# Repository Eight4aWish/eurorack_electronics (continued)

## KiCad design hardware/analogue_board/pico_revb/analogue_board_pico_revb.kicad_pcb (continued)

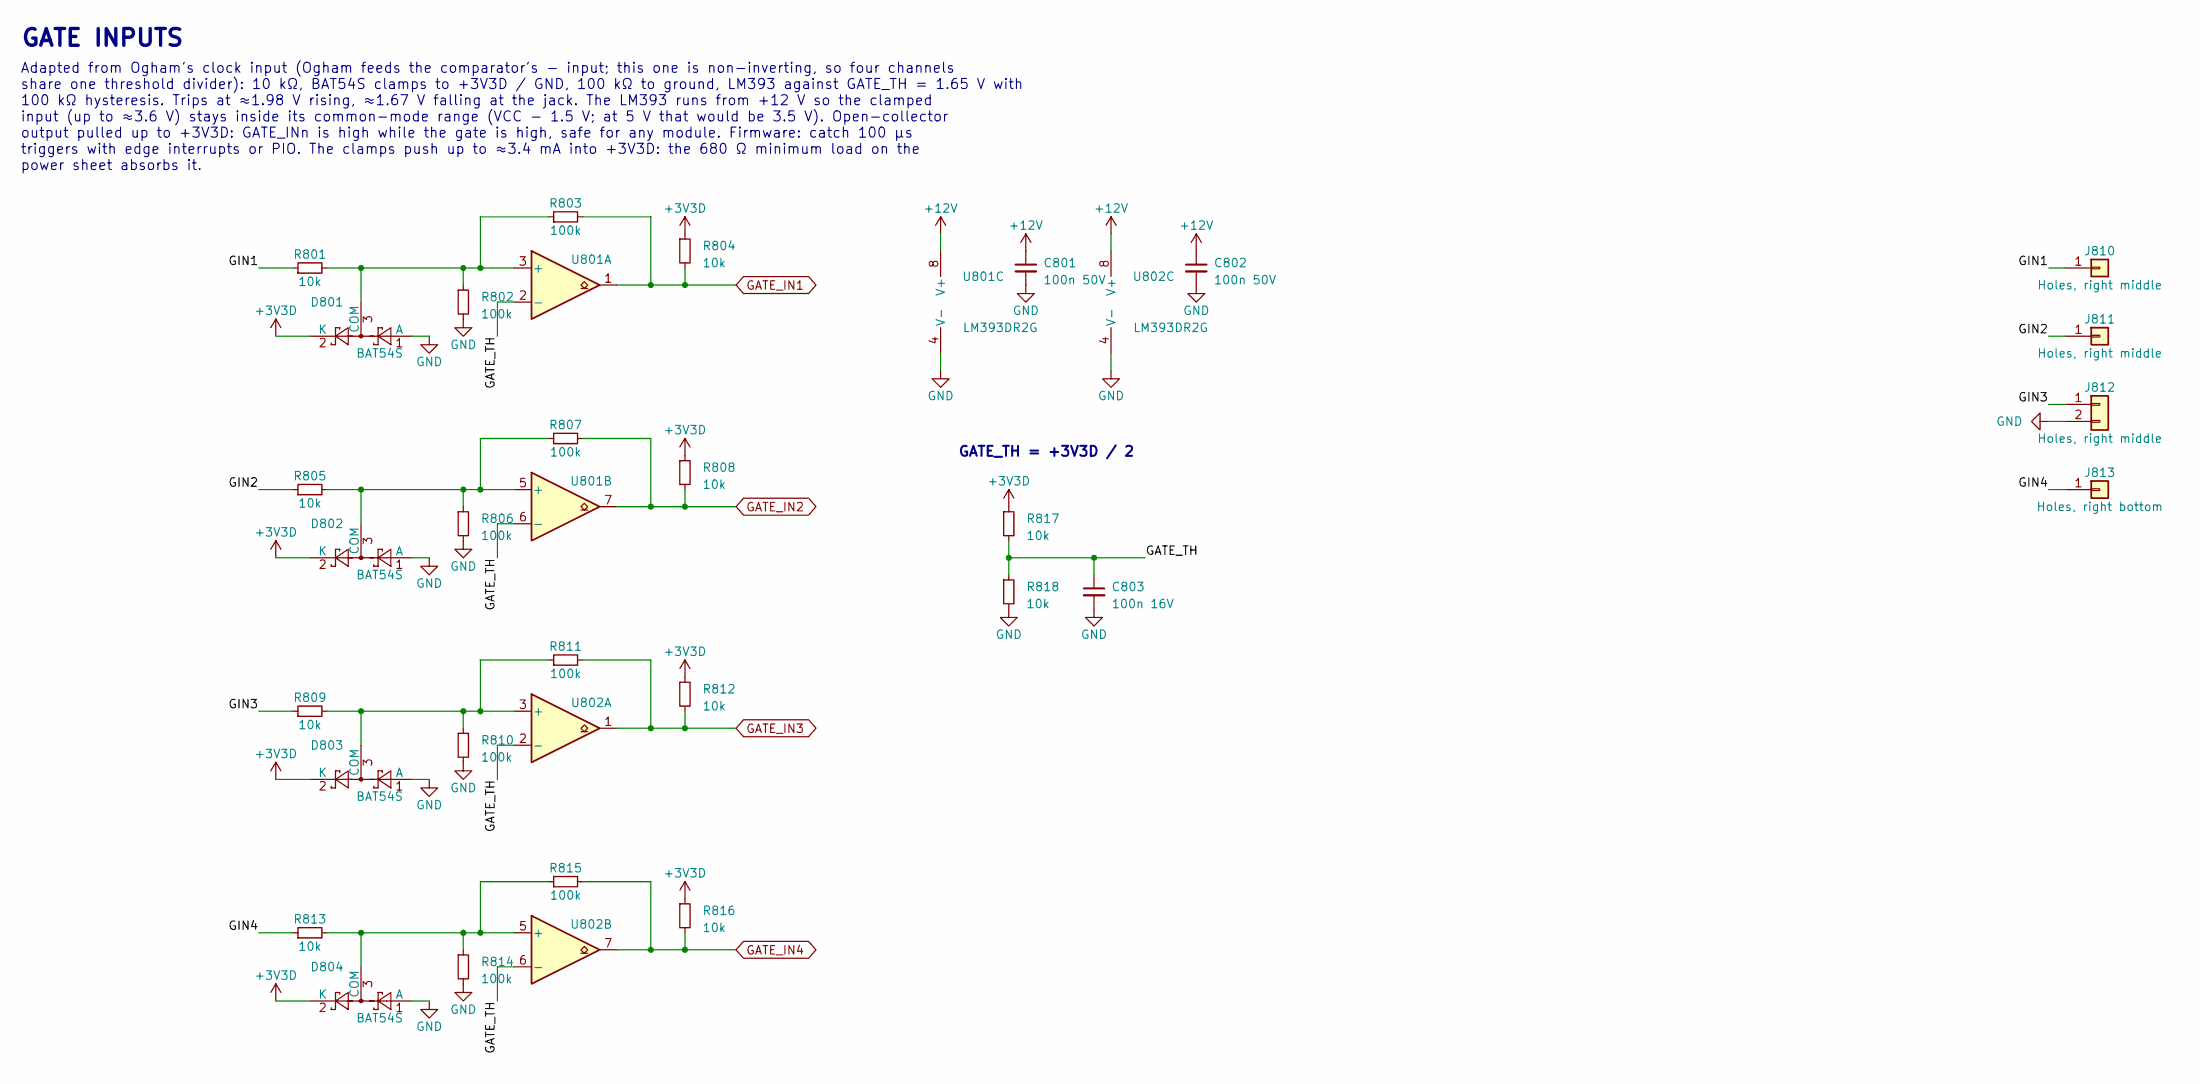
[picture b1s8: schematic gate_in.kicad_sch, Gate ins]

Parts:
C801, C802: 100n 50V; C_0603_1608Metric; Voltage 50V; LCSC C14663
C803: 100n 16V; C_0402_1005Metric; Voltage 16V; LCSC C1525
D801, D802, D803, D804: BAT54S; SOT-23; MPN BAT54S; LCSC C408389
J810, J811: Holes, right middle; WiringHoles_1x01; JLC bare holes
J812: Holes, right middle; WiringHoles_1x02_G2; JLC bare holes
J813: Holes, right bottom; WiringHoles_1x01; JLC bare holes
R801, R804, R805, R808, R809, R812, R813, R816, R817, R818: 10k; R_0402_1005Metric; Tolerance 1%; LCSC C25744
R802, R803, R806, R807, R810, R811, R814, R815: 100k; R_0402_1005Metric; Tolerance 1%; LCSC C25741
U801, U802: LM393DR2G; SOIC-8_3.9x4.9mm_P1.27mm; MPN LM393DR2G; LCSC C7955

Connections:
+3V3D: D801.2 (K), D802.2 (K), D803.2 (K), D804.2 (K), R804.1, R808.1, R812.1, R816.1, R817.1; also elsewhere on the board
+12V: C801.1, C802.1, U801.8 (V+), U802.8 (V+); also elsewhere on the board
/Gate ins/GATE_TH: C803.1, R817.2, R818.1, U801.2 (-), U801.6 (-), U802.2 (-), U802.6 (-)
/Gate ins/GIN1: J810.1, R801.1
/Gate ins/GIN2: J811.1, R805.1
/Gate ins/GIN3: J812.1, R809.1
/Gate ins/GIN4: J813.1, R813.1
GATE_IN1: R803.2, R804.2, U801.1; also elsewhere on the board
GATE_IN2: R807.2, R808.2, U801.7; also elsewhere on the board
GATE_IN3: R811.2, R812.2, U802.1; also elsewhere on the board
GATE_IN4: R815.2, R816.2, U802.7; also elsewhere on the board
GND: C801.2, C802.2, C803.2, D801.1 (A), D802.1 (A), D803.1 (A), D804.1 (A), J812.2, R802.2, R806.2, R810.2, R814.2, R818.2, U801.4 (V-), U802.4 (V-); also elsewhere on the board
unnamed: D801.3 (COM), R801.2, R802.1, R803.1, U801.3 (+)
unnamed: D802.3 (COM), R805.2, R806.1, R807.1, U801.5 (+)
unnamed: D803.3 (COM), R809.2, R810.1, R811.1, U802.3 (+)
unnamed: D804.3 (COM), R813.2, R814.1, R815.1, U802.5 (+)

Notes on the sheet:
GATE INPUTS
Adapted from Ogham's clock input (Ogham feeds the comparator's − input; this one is non-inverting, so four channels share one threshold divider): 10 kΩ, BAT54S clamps to +3V3D / GND, 100 kΩ to ground, LM393 against GATE_TH = 1.65 V with 100 kΩ hysteresis. Trips at ≈1.98 V rising, ≈1.67 V falling at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
GATE_TH = +3V3D / 2

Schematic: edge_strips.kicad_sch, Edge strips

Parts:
FID901, FID902, FID903: Fiducial; Fiducial_1mm_Mask2mm; JLC bare pad
J901: Edge strip, left (10HP); EdgeStrip_40_Left_10HP; JLC bare holes
J902: Edge strip, right; EdgeStrip_40_Right; JLC bare holes

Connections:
/Edge strips/DECK_L1: J901.1 (D1), J901.41 (W1)
/Edge strips/DECK_L2: J901.2 (D2), J901.42 (W2)
/Edge strips/DECK_L3: J901.3 (D3), J901.43 (W3)
/Edge strips/DECK_L4: J901.4 (D4), J901.44 (W4)
/Edge strips/DECK_L5: J901.5 (D5), J901.45 (W5)
/Edge strips/DECK_L6: J901.6 (D6), J901.46 (W6)
/Edge strips/DECK_L7: J901.7 (D7), J901.47 (W7)
/Edge strips/DECK_L8: J901.8 (D8), J901.48 (W8)
/Edge strips/DECK_L9: J901.9 (D9), J901.49 (W9)
/Edge strips/DECK_L17: J901.17 (D17), J901.57 (W17)
/Edge strips/DECK_L18: J901.18 (D18), J901.58 (W18)
/Edge strips/DECK_L19: J901.19 (D19), J901.59 (W19)
/Edge strips/DECK_L20: J901.20 (D20), J901.60 (W20)
/Edge strips/DECK_L21: J901.21 (D21), J901.61 (W21)
/Edge strips/DECK_L22: J901.22 (D22), J901.62 (W22)
/Edge strips/DECK_L23: J901.23 (D23), J901.63 (W23)
/Edge strips/DECK_L24: J901.24 (D24), J901.64 (W24)
/Edge strips/DECK_L25: J901.25 (D25), J901.65 (W25)
/Edge strips/DECK_L32: J901.32 (D32), J901.72 (W32)
/Edge strips/DECK_L33: J901.33 (D33), J901.73 (W33)
/Edge strips/DECK_L34: J901.34 (D34), J901.74 (W34)
/Edge strips/DECK_L35: J901.35 (D35), J901.75 (W35)
/Edge strips/DECK_L36: J901.36 (D36), J901.76 (W36)
/Edge strips/DECK_L37: J901.37 (D37), J901.77 (W37)
/Edge strips/DECK_L38: J901.38 (D38), J901.78 (W38)
/Edge strips/DECK_L39: J901.39 (D39), J901.79 (W39)
/Edge strips/DECK_L40: J901.40 (D40), J901.80 (W40)
/Edge strips/DECK_R1: J902.1 (D1), J902.41 (W1)
/Edge strips/DECK_R2: J902.2 (D2), J902.42 (W2)
/Edge strips/DECK_R3: J902.3 (D3), J902.43 (W3)
/Edge strips/DECK_R4: J902.4 (D4), J902.44 (W4)
/Edge strips/DECK_R5: J902.5 (D5), J902.45 (W5)
/Edge strips/DECK_R6: J902.6 (D6), J902.46 (W6)
/Edge strips/DECK_R7: J902.7 (D7), J902.47 (W7)
/Edge strips/DECK_R8: J902.8 (D8), J902.48 (W8)
/Edge strips/DECK_R9: J902.9 (D9), J902.49 (W9)
/Edge strips/DECK_R17: J902.17 (D17), J902.57 (W17)
/Edge strips/DECK_R18: J902.18 (D18), J902.58 (W18)
/Edge strips/DECK_R19: J902.19 (D19), J902.59 (W19)
/Edge strips/DECK_R20: J902.20 (D20), J902.60 (W20)
/Edge strips/DECK_R21: J902.21 (D21), J902.61 (W21)
/Edge strips/DECK_R22: J902.22 (D22), J902.62 (W22)
/Edge strips/DECK_R23: J902.23 (D23), J902.63 (W23)
/Edge strips/DECK_R24: J902.24 (D24), J902.64 (W24)
/Edge strips/DECK_R25: J902.25 (D25), J902.65 (W25)
/Edge strips/DECK_R32: J902.32 (D32), J902.72 (W32)
/Edge strips/DECK_R33: J902.33 (D33), J902.73 (W33)
/Edge strips/DECK_R34: J902.34 (D34), J902.74 (W34)
/Edge strips/DECK_R35: J902.35 (D35), J902.75 (W35)
/Edge strips/DECK_R36: J902.36 (D36), J902.76 (W36)
/Edge strips/DECK_R37: J902.37 (D37), J902.77 (W37)
/Edge strips/DECK_R38: J902.38 (D38), J902.78 (W38)
/Edge strips/DECK_R39: J902.39 (D39), J902.79 (W39)
/Edge strips/DECK_R40: J902.40 (D40), J902.80 (W40)

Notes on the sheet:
EDGE STRIPS
Two n8synth-style edge strips, 40 positions each at 2.54 mm. Each position is an outer hole (the deck's header pin, Dn) joined to an inner hole (a wiring point, Wn) by the net DECK_Ln / DECK_Rn: one pin per hole. Nothing else on the board connects to them: each module is wired by hand from the chan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
Fiducials for JLCPCB assembly
Hardware licence: CC BY-SA 4.0 (LICENSE in hardware/analogue_board).

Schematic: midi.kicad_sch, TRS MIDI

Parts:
C1001, C1002: 100n 16V; C_0402_1005Metric; Voltage 16V; LCSC C1525
C1003: 100n 50V; C_0603_1608Metric; Voltage 50V; LCSC C14663
D1001: BAT54S; SOT-23; MPN BAT54S; LCSC C408389
D1002: 1N4148WS; D_SOD-323; MPN 1N4148WS; LCSC C2128
J1001: TRS MIDI out holes; WiringHoles_1x02; JLC bare holes
J1002: TRS MIDI in holes; WiringHoles_1x03; JLC bare holes
R1001, R1008, R1009: 1k; R_0402_1005Metric; Tolerance 1%; LCSC C11702
R1002: 10k; R_0402_1005Metric; Tolerance 1%; LCSC C25744
R1003, R1004, R1005, R1006: 100R; R_1206_3216Metric; Tolerance 1%; LCSC C17901
R1007: 220R; R_0805_2012Metric; Tolerance 1%; LCSC C17557
U1001: SN74AHCT1G125DBVR; SOT-23-5; MPN SN74AHCT1G125DBVR; LCSC C7484
U1002: H11L1SR2M; SMDIP-6_W9.53mm; MPN H11L1SR2M; LCSC C20082

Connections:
+3V3D: C1002.1, R1002.1, R1008.1, U1002.6; also elsewhere on the board
+5VD: C1001.1, D1001.2 (K), R1005.1, U1001.5 (VCC); also elsewhere on the board
/TRS MIDI/MI_R: J1002.2, R1007.1
/TRS MIDI/MI_S: C1003.1, J1002.3
/TRS MIDI/MI_T: D1002.2 (A), J1002.1, U1002.2
/TRS MIDI/MO_R: J1001.2, R1006.2
/TRS MIDI/MO_T: J1001.1, R1004.2
GND: C1001.2, C1002.2, C1003.2, D1001.1 (A), U1001.1, U1001.3 (GND), U1002.5; also elsewhere on the board
MIDI_RX: R1009.2; also elsewhere on the board
MIDI_TX: R1001.1; also elsewhere on the board
unnamed: D1001.3 (COM), R1003.1, U1001.4
unnamed: D1002.1 (K), R1007.2, U1002.1
unnamed: R1001.2, R1002.2, U1001.2
unnamed: R1003.2, R1004.1
unnamed: R1005.2, R1006.1
unnamed: R1008.2, R1009.1, U1002.4

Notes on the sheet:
TRS MIDI IN AND OUT
MIDI 1.0 over 3.5 mm TRS, Type A (MIDI Association RP-054): tip = current sink (DIN pin 5), ring = current source (DIN pin 4), sleeve = shield (DIN pin 2). Electrical values per CA-033 (2014). Wired straight to the module's UART pins 1 and 2 (TX, RX), with no links. Review: docs/analogue_board_revi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
MIDI OUT: 3.3 V UART → 74AHCT1G125 at +5VD → 2 × 100 Ω per leg (1206) → TRS. Idle high = no loop current. A mono cable shorting ring to sleeve draws 25 mA from the buck; each 100 Ω sees 64 mW.
MIDI IN: ring → 220 Ω → H11L1 LED → tip; 1N4148WS across the LED for reverse polarity. H11L1 switches at 1.6 mA (a worst-case 3.3 V sender still gives ≈4.5 mA). Output pulled up by 1 kΩ to +3V3D, then 1 kΩ to the module pin. The IN jack's sleeve is NOT grounded (CA-033: no ground loop): wire it to 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
WIRING (two stereo jacks in deck cells): OUT: tip → MO_T, ring → MO_R, sleeve → the deck's D (ground) pad. IN: tip → MI_T, ring → MI_R, sleeve → MI_S or open: NOT to D. Type B gear: swap that jack's tip and ring wires. Bring-up: loop OUT to IN with a stereo cable; ≈1.2-1.3 V across the 220 Ω while 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

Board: 4 copper layers, 361 parts (177 on the bottom side), 249 nets, no tracks yet.

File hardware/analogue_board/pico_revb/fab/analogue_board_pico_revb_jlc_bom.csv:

Comment,Designator,Footprint,LCSC Part #
10u 50V,"C201,C203,C205,C206",C_1206_3216Metric,C13585
100n 50V,"C202,C204,C207,C215,C319,C320,C416,C417,C419,C420,C512,C513,C514,C515,C801,C802,C1003",C_0603_1608Metric,C14663
100n 16V,"C208,C212,C217,C302,C304,C306,C309,C312,C405,C418,C421,C502,C602,C604,C605,C606,C607,C608,C609,C610,C611,C701,C702,C703,C704,C705,C708,C709,C803,C1001,C1002",C_0402_1005Metric,C1525
22u 25V,"C210,C211,C407",C_1206_3216Metric,C12891
10u 25V,"C213,C216,C219,C221,C222,C301,C303,C305,C403,C404,C408,C501,C603",C_0805_2012Metric,C15850
1u 50V,"C214,C401,C402,C406",C_0603_1608Metric,C15849
1u 25V,"C218,C220,C503,C601",C_0402_1005Metric,C52923
100p 50V,"C307,C310,C313,C314,C316,C317,C505,C506,C507,C508,C509,C510,C511",C_0402_1005Metric,C1546
1u 50V,"C308,C311",C_0805_2012Metric,C28323
1n C0G 50V,"C315,C318",C_0603_1608Metric,C106246
1n 50V,"C409,C410,C411,C412,C413,C414,C415,C504",C_0402_1005Metric,C1523
10n 50V,"C706,C707",C_0402_1005Metric,C15195
47u 10V,C710,C_1206_3216Metric,C96123
SS34,"D201,D202,D203",D_SMA,C8678
BAT54S,"D301,D302,D801,D802,D803,D804,D1001",SOT-23,C408389
PESD15VL1BA,"D401,D402,D403,D404,D405,D406,D407",D_SOD-323,C85378
BAV99,"D601,D602,D603,D604",SOT-23,C2500
1N4148WS,D1002,D_SOD-323,C2128
BLM18PG121,"FB201,FB202,FB203,FB301",L_0603_1608Metric,C14709
15uH,L201,L_Sunlord_SWPA5040S,C44888
AO3401A,Q201,SOT-23,C15127
510k,R201,R_0603_1608Metric,C23192
75k,"R202,R505,R507,R509,R511,R513,R515,R518",R_0603_1608Metric,C23242
15k,"R203,R307,R311,R502",R_0402_1005Metric,C25756
2k,R204,R_0402_1005Metric,C4109
0R,R206,R_0805_2012Metric,C17477
0R,"R207,R208,R209",R_0603_1608Metric,C21189
680R,R210,R_0603_1608Metric,C23228
1M,"R211,R309,R313,R604,R606,R608,R610,R612,R614",R_0402_1005Metric,C26083
100k,"R212,R308,R312,R405,R409,R413,R417,R421,R425,R429,R802,R803,R806,R807,R810,R811,R814,R815",R_0402_1005Metric,C25741
10k,"R301,R302,R303,R401,R402,R403,R501,R504,R506,R508,R510,R512,R514,R516,R602,R615,R616,R702,R704,R706,R708,R710,R712,R801,R804,R805,R808,R809,R812,R813,R816,R817,R818,R1002",R_0402_1005Metric,C25744
5.1R,R304,R_0603_1608Metric,C25197
1k,"R305,R310,R314,R317,R318,R324,R325,R404,R408,R412,R416,R420,R424,R428,R603,R605,R607,R609,R611,R613,R617,R618,R619,R620,R701,R703,R705,R707,R709,R711,R1001,R1008,R1009",R_0402_1005Metric,C11702
220k,R306,R_0603_1608Metric,C22961
12k,"R315,R316,R322,R323",R_0402_1005Metric,C25752
30k,"R319,R320,R326,R327",R_0603_1608Metric,C22984
1k,"R321,R328,R406,R410,R414,R418,R422,R426,R517",R_1206_3216Metric,C4410
4.7k,"R407,R411,R415,R419,R423,R427",R_0402_1005Metric,C25900
20k,R503,R_0402_1005Metric,C25765
100R,R601,R_0805_2012Metric,C17408
2.2k,"R713,R714",R_0402_1005Metric,C25879
330R,R715,R_0402_1005Metric,C25104
100R,"R1003,R1004,R1005,R1006",R_1206_3216Metric,C17901
220R,R1007,R_0805_2012Metric,C17557
TPS54308DDCR,U201,SOT-23-6,C168839
L78M05ABDT-TR,U202,TO-252-2_PasteShapes,C58069
XC6206P332MR-G,"U203,U204",SOT-23,C5446
PCM3060PWR,U301,TSSOP-28_4.4x9.7mm_P0.65mm,C2651841
TL074HIDR,"U302,U502,U504",SOIC-14_3.9x8.7mm_P1.27mm,C2878713
ADS8688IDBTR,U401,TSSOP-38_4.4x9.7mm_P0.5mm,C527390
DG412DQ-T1-E3,"U402,U403",TSSOP-16_4.4x5mm_P0.65mm,C2651920
DAC8568IAPWR,U501,TSSOP-16_4.4x5mm_P0.65mm,C486051
MCP3208-CI/SL,U601,SOIC-16_3.9x9.9mm_P1.27mm,C16939
74HCT595PW,U602,TSSOP-16_4.4x5mm_P0.65mm,C99710
TCA9555PWR,U701,TSSOP-24_4.4x7.8mm_P0.65mm,C465732
M24C64-RMN6TP,U702,SOIC-8_3.9x4.9mm_P1.27mm,C79988
SN74AHCT1G125DBVR,"U703,U1001",SOT-23-5,C7484
LM393DR2G,"U801,U802",SOIC-8_3.9x4.9mm_P1.27mm,C7955
H11L1SR2M,U1002,SMDIP-6_W9.53mm,C20082

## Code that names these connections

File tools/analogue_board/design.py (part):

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         "+5VA": "power:+5VA", "+3V3A": "power:+3.3VA", "+3V3D": "power:+3V3", "MOD_5V": "power:+5V"}

# Module pin map. One row per module-facing net: function, Pico 2 pin (GPIO), Teensy 4.1 pin, why.
# Pico: SPI0/SPI1/I2C1/UART0 per the RP2350 GPIO function table; I2S runs on PIO (BCK, LRCK on
# consecutive pins for side-set), MCLK from CLK_GPOUT0. Teensy: fixed peripheral pins from the
# PJRC card (SPI, SPI1, SAI1, Wire, Serial1, Serial4).
PINMAP = [
    ("MCLK", "I2S master clock to SCKI1/2", 27, "GP21", "23", "Pico CLK_GPOUT0 · Teensy MCLK1"),
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    ("CS_DAC", "DAC8568 SYNC", 26, "GP20", "9", ""),
    ("SPIB_SCK", "Panel bus clock", 14, "GP10", "27", "Pico SPI1 SCK · Teensy SCK1"),
    ("SPIB_MOSI", "Panel bus data out", 15, "GP11", "26", "Pico SPI1 TX · Teensy MOSI1"),
    ("SPIB_MISO", "Panel bus data in (MCP3208)", 16, "GP12", "39", "Pico SPI1 RX · Teensy MISO1 (alt pin)"),
    ("CS_595", "74HCT595 latch (RCLK)", 17, "GP13", "38", ""),
    ("CS_POT", "MCP3208 chip select", 19, "GP14", "37", ""),
    ("SDA", "I2C data", 4, "GP2", "18", "Pico I2C1 SDA · Teensy SDA (Wire)"),
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]
# Rev B, the Pico 2 / ESP32-P4 board alone (docs/analogue_board_revb.md §1, §3; David, 2026-10-25).
# Pins 16 and 17 are the ESP32-P4's own I2C (its camera, display and ES8311 codec): they go to two
# holes and nothing else, on every board. CS_595 takes pin 20, free since jack detect went. The
# pots ADC keeps the panel bus (spec §6.1: the converter bus is the CV converters' alone), so its
# data line moves to GP8, the Pico's other SPI1 RX pin: EXP_INT is dropped (the firmware polls the
# TCA9555) and gate input 3 takes its pin. SPIA_MISO and CS_DAC swap, so that pins 21, 22 and 24,
# on the ESP32-P4's programmable VDD_IO_5 bank, carry only signals the module drives.
_REVB_PINS = {"GATE_IN3": (6, "GP4", ""), "SPIB_MISO": (11, "GP8", "Pico SPI1 RX"), "CS_595": (20, "GP15", ""),
              "CS_DAC": (21, "GP16", ""), "SPIA_MISO": (26, "GP20", "Pico SPI0 RX")}
PINMAP_REVB = [(net, func, *_REVB_PINS[net][:2], tl, _REVB_PINS[net][2]) if net in _REVB_PINS else (net, func, pin, gp, tl, note)
               for net, func, pin, gp, tl, note in PINMAP if net != "EXP_INT"] + [
    ("P4_SCL", "ESP32-P4's own I2C clock: hole J102 only", 16, "GP12", "", "Pico reserved: ESP32-P4 GPIO8"),
    ("P4_SDA", "ESP32-P4's own I2C data: hole J102 only", 17, "GP13", "", "Pico reserved: ESP32-P4 GPIO7"),
]
# MIDI wired straight to the UART pins (David, 2026-11-02): no link holes, so no spare GPIO
_MIDI_PINS = {"SPARE1": ("MIDI_TX", "MIDI out (UART TX)"), "SPARE2": ("MIDI_RX", "MIDI in (UART RX)")}
if variant.MIDI_DIRECT:
    PINMAP_REVB = [(*_MIDI_PINS[net], pin, gp, tl, note) if net in _MIDI_PINS else (net, func, pin, gp, tl, note)
                   for net, func, pin, gp, tl, note in PINMAP_REVB]
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
def J101_NETS():
    """Spare GPIO and MIDI links (without TRS MIDI, the spare pins alone); the Pico (and ESP32-P4)
    also brings its RUN (reset) pin out. With MIDI wired straight, RUN and GND are all that is left."""
    spares = ([] if variant.MIDI_DIRECT else ["SPARE1", "MIDI_TX", "SPARE2", "MIDI_RX"] if variant.has("midi")
              else ["SPARE1", "SPARE2"])
    return spares + (["RUN"] if PICO else []) + ["GND"]
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        nets.update({30: "RUN", 39: "MOD_5V", 40: "PICO_VBUS"})
        for n in range(1, 41):
            nets.setdefault(n, NC)   # ADC_VREF, 3V3_OUT, 3V3_EN and the pin jack detect used (GP15)
        ic(sh, "PICO2", (75, 110), nets, ref=variant.REF["pico"], stubs={30: 12.7})  # RUN label clear of BCK
    if TEENSY:
        lines += ["Teensy 4.1 (not 5 V tolerant): cut the VIN–VUSB pads before fitting; VIN takes MOD_5V.",
                  "Shortened headers on pins 1-19 and 29-48: pins 20-28 have no holes on this board."
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            nets[by_label[tlabel]] = net
        for n, lab in tpins.items():
            if n not in nets:
                nets[n] = "GND" if lab == "GND" else "MOD_5V" if lab == "VIN" else NC   # 3V3 outputs, unused GPIO
        ic(sh, "TEENSY41", (185 if both else 90, 115), nets, ref=variant.REF["teensy"], p=dict(ICS["TEENSY41"], fp=TEENSY_FP))
    sh.text("\n".join(lines), (20, 24), size=1.6)

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        sh.text("MIDI is wired straight to pins 1 and 2 (UART0 TX, RX): move the SDK console\noff UART0 to USB. "
                "RUN: wire a reset button to GND (Pico or ESP32-P4).", (85, 162), size=1.27)
    else:
        holes(sh, (75, 170.18), j101, "Spare GPIO" + (", MIDI links" if midi else "") + (", RUN" if PICO else ""), ref="J101",
              stubs={j101.index("RUN") + 1: 15.24} if PICO else None)
        sh.text(("MIDI: bridge SPARE1-MIDI_TX and SPARE2-MIDI_RX (adjacent holes)\nwith a wire or shunt. Left open, SPARE1/2 are plain GPIO.\n"
                 if midi else "SPARE1/2: plain GPIO (UART0 TX/RX on a Pico, Serial1 on a Teensy).\n")
                + ("On a Pico, move the SDK console off UART0 to USB.\nRUN: wire a reset button to GND (Pico or ESP32-P4)." if PICO
                   else "On a Teensy they are Serial1 (TX1, RX1)."), (85, 162), size=1.27)
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    rows = [["Net", "Function", *cols, "Why this pin"]]
    for net, func, pin, gpio, tl, note in PINMAP:
        rows.append([net, func, *([f"{gpio} (pin {pin})"] if PICO else []), *([f"D{tl}"] if TEENSY else []), note_for(note)])
    rows.append(["MOD_5V", "Module 5 V in", *(["VSYS (pin 39)"] if PICO else []), *(["VIN"] if TEENSY else []),
                 "Schottky D203" + ("; Q201 bypass if JP201" if PICO else "")])
    if PICO:
        rows.append(["PICO_VBUS", "Module USB 5 V sense", "VBUS (pin 40)", *(["—"] if TEENSY else []), "Q201 gate: off with USB plugged in"])
        rows.append(["RUN", "Module reset", "RUN (pin 30)", *(["—"] if TEENSY else []), f"To hole J101-{j101.index('RUN') + 1}"])
    sh.text("PIN MAP", (238, 18), size=2.0, bold=True)
    sh.table((238, 22), [22, 50, 25, 17, 52] if both else [22, 50, 25, 69], rows, row_h=5.08)

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    sh.wire(vin, fbin.p("2"))
    sh.wire(fbin.p("1"), (fbin.p("1")[0] - 5.08, vin[1]))
    sh.power("+12V", (fbin.p("1")[0] - 5.08, vin[1]))
    sh.label("BUCK_VIN", (vin[0] - 5.08, vin[1]), 90)
    sh.tie("+12V", (fbin, "1"))
    sh.tie("BUCK_VIN", (fbin, "2"), (u, "3"))
    for i, (v, sz) in enumerate([("10u", "1206"), ("10u", "1206"), ("100n", "0603")]):
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    sh.connect(r, 1, "MOD_5V", stub=0)
    sh.wire(r.p("2"), nv)
    sh.wire((nv[0] - 5.08, gy), nv)
    sh.label("PICO_VBUS", (nv[0] - 5.08, gy), 180, kind="global")
    jp = part(sh, "SJ_OPEN", (mx + 44.45, gy), ref="JP201", value="ESP32-P4: bridge")
    sh.wire(nv, jp.p("1"))
    sh.wire(jp.p("2"), nf)
    sh.label("FET_EN", nf, 0)
    r2 = R(sh, "100k", (nf[0], gy + 5.08))
    sh.wire(nf, r2.p("1"))
    sh.connect(r2, 2, "GND", stub=0)
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
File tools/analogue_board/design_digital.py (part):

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    ic(sh, "MCP3208", (55.88, 83.82), adc, ref="U601")
    decaps(sh, 30.48, 116.84, "+3V3A", [("1u", "0402"), ("100n", "0402")], "U601 VDD pin 16")
    for i, (v, sz) in enumerate([("10u", "0805"), ("100n", "0402")]):
        c = C(sh, v, (60.96 + i * 12.7, 124.46), size=sz, decouples="U601 VREF pin 15 (POT_REF)")
        if i == 0:
            sh.flagged_stub(c, 1, "POT_REF")
        else:
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    exp.update({pin: NC for pin, net in exp.items() if net.startswith("BTN") and int(net[3:]) > variant.SWITCHES})
    if not variant.has("exp_int"):   # Rev B: the firmware polls the expander; INT (open drain) is left open
        exp[1] = NC
    ic(sh, "TCA9555", (68.58, 101.6), exp, ref="U701", stubs={11: 17.78})  # BTN9 label past the GATE_OE_N label
    decap(sh, (45.72, 139.7), "100n", "0402", "+3V3D", "U701 VCC pin 24")
    if variant.has("exp_int"):
        r = R(sh, "10k", (30.48, 76.2), fields={"Note": "INT is open-drain"})
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           stubs={1: 7.62, 4: 5.08}, **AHCT_TEXT(281.94, 190.5))
    decap(sh, (256.54, 213.36), "100n", "0402", "+5VD", "U703 VCC pin 5")
    r = R(sh, "330R", (317.5, 190.5), rot=90)
    sh.wire((u.p("4")[0] + 5.08, 190.5), r.p("1"))  # one LED_BUF label over a continuous wire
    sh.tie("LED_BUF", (r, "1"))
    sh.connect(r, 2, "LED_DIN")
    holes(sh, (350.52, 190.5), ["LED_DIN", "+5VD", "+5VD", "GND", "GND"], "WS2812 chain holes", ref="J704")
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        sh.connect(rpu, "1", "+3V3D", stub=0)
        sh.label(f"GATE_IN{n}", (o[0] + 12.7, out[1]), 0, kind="global")
        sh.wire(minus, (minus[0] - 2.54, minus[1]), (minus[0] - 2.54, minus[1] + 5.08))
        sh.label("GATE_TH", (minus[0] - 2.54, minus[1] + 5.08), 270)
        sh.tie(f"GIN{n}", (rin, "1"))
        sh.tie(f"GIN{n}_CMP", (rin, "2"), (d, "3"), (rpd, "1"), (rh, "1"), (u, pp))
        sh.tie(f"GATE_IN{n}", (u, po), (rh, "2"), (rpu, "2"))
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    sh.wire(rt.p("2"), rb.p("1"))
    sh.wire((167.64, 96.52), (180.34, 96.52), c.p("1"))
    sh.wire((180.34, 96.52), (187.96, 96.52))
    sh.label("GATE_TH", (187.96, 96.52), 0)
    sh.connect(rb, 2, "GND", stub=0)
    sh.connect(c, 2, "GND", stub=0)
    sh.tie("GATE_TH", (rt, "2"), (rb, "1"), (c, "1"))
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    sh.text("MIDI 1.0 over 3.5 mm TRS, Type A (MIDI Association RP-054): tip = current sink (DIN pin 5), ring = current source\n"
            "(DIN pin 4), sleeve = shield (DIN pin 2). Electrical values per CA-033 (2014). "
            + ("Wired straight to the module's UART pins 1 and 2\n(TX, RX), with no links. " if variant.MIDI_DIRECT else
               "Uses the two UART-capable spare pins through\nlink holes on J101 (SPARE1-MIDI_TX, SPARE2-MIDI_RX): left open, SPARE1/2 stay plain GPIO. ")
            + "Review: docs/analogue_board_review/midi.md",
            (20, 23), size=1.5)

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    sh.text("MIDI OUT: 3.3 V UART → 74AHCT1G125 at +5VD → 2 × 100 Ω per leg (1206) → TRS. Idle high = no loop current.\n"
            "A mono cable shorting ring to sleeve draws 25 mA from the buck; each 100 Ω sees 64 mW.", (20, 46), size=1.27)
    sh.wire((43.18, yo), (45.72, yo))
    sh.label("MIDI_TX", (43.18, yo), 180, kind="global")
    r1 = R(sh, "1k", (48.26, yo), rot=90, fields={"Note": "limits current into the buffer input from the module pin"})
    u = part(sh, "AHCT1G125", (73.66, yo), **AHCT_TEXT(73.66, yo))
    a = u.p("2")
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    sh.wire(y, node, ra.p("1"))
    sh.wire(ra.p("2"), rb.p("1"))
    sh.wire(rb.p("2"), (rb.p("2")[0] + 5.08, yo))
    sh.label("MO_T", (rb.p("2")[0] + 5.08, yo), 0)
    d = clamp_below(sh, "BAT54S", node, "+5VD")
    sh.tie("MIDI_DRV", (u, "4"), (ra, "1"), (d, "3"))
    sh.tie("MIDI_TIP_MID", (ra, "2"), (rb, "1"))
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    sh.wire((node[0], yr), rc.p("1"))
    sh.wire(rc.p("2"), rd.p("1"))
    sh.wire(rd.p("2"), (rd.p("2")[0] + 5.08, yr))
    sh.label("MO_R", (rd.p("2")[0] + 5.08, yr), 0)
    sh.tie("+5VD", (rc, "1"))
    sh.tie("MIDI_RING_MID", (rc, "2"), (rd, "1"))
    sh.tie("MO_R", (rd, "2"))
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    p1, p2 = opto.p("1"), opto.p("2")
    rin = R(sh, "220R", (60.96, yi - 5.08), rot=90, size="0805", fields={"Note": "MIDI IN current limit (CA-033)"})
    sh.wire((43.18, yi - 5.08), rin.p("1"))
    sh.label("MI_R", (43.18, yi - 5.08), 180)
    sh.wire(rin.p("2"), (78.74, yi - 5.08), (78.74, p1[1]), p1)
    sh.wire((43.18, yi + 5.08), (78.74, yi + 5.08), (78.74, p2[1]), p2)
    sh.label("MI_T", (43.18, yi + 5.08), 180)
    dr = part(sh, "1N4148WS", (71.12, yi), rot=270, text_left=True)
    sh.wire((71.12, yi - 5.08), dr.p("1"))
    sh.wire(dr.p("2"), (71.12, yi + 5.08))
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    sh.wire(rxo, rpu.p("2"))
    sh.connect(rpu, "1", "+3V3D", stub=0)
    sh.wire(rs.p("2"), (rs.p("2")[0] + 5.08, yi))
    sh.label("MIDI_RX", (rs.p("2")[0] + 5.08, yi), 0, kind="global")
    sh.tie("MIDI_RXO", (opto, "4"), (rpu, "2"), (rs, "1"))
    sh.tie("MIDI_RX", (rs, "2"))
    decap(sh, (127, 147.32), "100n", "0402", "+3V3D", f"{opto.ref} VCC pin 6")
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
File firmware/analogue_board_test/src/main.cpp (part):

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#include <Wire.h>

// ---- pins (Teensy numbering)
constexpr uint8_t PIN_CS_ADC = 10, PIN_CS_DAC = 9;                      // SPI-A: SCK 13, MOSI 11, MISO 12
constexpr uint8_t PIN_SPIB_MISO = 39, PIN_CS_595 = 38, PIN_CS_POT = 37;  // SPI-B (SPI1): SCK 27, MOSI 26
constexpr uint8_t PIN_EXP_INT = 22, PIN_LED_DATA = 17;                  // I2S on 23/21/20/7/8, I2C on 18/19
constexpr uint8_t PIN_GATE_IN[4] = {2, 3, 4, 5};
// every board net on the module except SDA/SCL: inputs at boot (MIDI is Serial1 on 0 and 1)
constexpr uint8_t BOARD_PINS[] = {13, 11, 12, 10, 9, 27, 26, 39, 38, 37, 23, 21, 20, 7, 8, 22, 17, 2, 3, 4, 5, 0, 1};
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constexpr int NUM_LEDS = 16;  // data for 16; a shorter chain shows the first few
static byte led_draw[NUM_LEDS * 3];
DMAMEM static byte led_frame[NUM_LEDS * 12];
static WS2812Serial leds(NUM_LEDS, led_frame, led_draw, PIN_LED_DATA, WS2812_GRB);
static QuadEncoder *enc;

// ---- serial
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// ---- SPI-A: ADS8688 and DAC8568
static void spia_start() {
  if (spia_ready) return;
  digitalWrite(PIN_CS_ADC, HIGH);
  pinMode(PIN_CS_ADC, OUTPUT);
  digitalWrite(PIN_CS_DAC, HIGH);
  pinMode(PIN_CS_DAC, OUTPUT);
  SPI.begin();
  spia_ready = true;
}

static uint16_t adc_frame(uint16_t cmd) {  // 32 clocks: a command in, the previous frame's conversion out
  SPI.beginTransaction(SPI_CONV);
  digitalWriteFast(PIN_CS_ADC, LOW);
  SPI.transfer16(cmd);
  uint16_t r = SPI.transfer16(0);
  digitalWriteFast(PIN_CS_ADC, HIGH);
  SPI.endTransaction();
  return r;
}

static uint8_t adc_reg(uint8_t reg, int val = -1) {  // read if val < 0; a write echoes the byte written
  SPI.beginTransaction(SPI_CONV);
  digitalWriteFast(PIN_CS_ADC, LOW);
  SPI.transfer16((reg << 9) | (val >= 0 ? 0x100 | val : 0));
  uint8_t r = SPI.transfer(0);
  digitalWriteFast(PIN_CS_ADC, HIGH);
  SPI.endTransaction();
  return r;
}
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
static void dac_frame(uint32_t w) {
  SPI.beginTransaction(SPI_CONV);
  digitalWriteFast(PIN_CS_DAC, LOW);
  SPI.transfer16(w >> 16);
  SPI.transfer16(w & 0xFFFF);
  digitalWriteFast(PIN_CS_DAC, HIGH);
  SPI.endTransaction();
}

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// ---- SPI-B: 74HCT595 and MCP3208
static void spib_start() {
  if (spib_ready) return;
  digitalWrite(PIN_CS_595, HIGH);
  pinMode(PIN_CS_595, OUTPUT);
  digitalWrite(PIN_CS_POT, HIGH);
  pinMode(PIN_CS_POT, OUTPUT);
  SPI1.setMISO(PIN_SPIB_MISO);
  SPI1.begin();
  spib_ready = true;
}
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  SPI1.beginTransaction(SPI_PANEL);
  SPI1.transfer(word);
  SPI1.endTransaction();
  digitalWriteFast(PIN_CS_595, LOW);  // RCLK: latches on the rising edge
  delayMicroseconds(1);
  digitalWriteFast(PIN_CS_595, HIGH);
}

static uint16_t pot_read(uint8_t ch) {  // MCP3208, single-ended: start, SGL, D2-D0, then 12 bits
  SPI1.beginTransaction(SPI_PANEL);
  digitalWriteFast(PIN_CS_POT, LOW);
  SPI1.transfer(0x06 | (ch >> 2));
  uint8_t hi = SPI1.transfer((ch & 3) << 6);
  uint8_t lo = SPI1.transfer(0);
  digitalWriteFast(PIN_CS_POT, HIGH);
  SPI1.endTransaction();
  return ((hi & 0x0F) << 8) | lo;
}
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static void block_encoder() {
  Serial.println("Block 12, encoder: A on GIN3, B on GIN1 (QuadEncoder), common to POT_REF; push through JPS2 to SW6");
  if (!enc_ready) {
    // GIN3 and GIN1, the holes nearest the encoder's cell on the agreed fit (2026-10-31); any gate-in pin works on a Teensy 4.1
    enc = new QuadEncoder(1, PIN_GATE_IN[2], PIN_GATE_IN[0], 0);  // no internal pull-ups: the LM393s have theirs
    enc->setInitConfig();
    enc->EncConfig.filterCount = 7;  // the longest input filter, against contact bounce
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
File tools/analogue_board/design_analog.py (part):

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        4: "LRCK", 5: "BCK", 6: "MCLK", 12: "I2S_DOUT", 11: "LRCK", 10: "BCK", 9: "MCLK",
        20: "VOUTL_P", 19: "VOUTL_N", 18: "VOUTR_P", 17: "VOUTR_N", 14: NC, 13: NC, 3: "I2S_DIN", 21: "VCOM",
        7: "CODEC_VDD", 24: "CODEC_VCC", 8: "GND", 16: "GND", 23: "GND", 22: "GND"}, ref="U301",
        stubs={24: 7.62, 16: 7.62, 22: 7.62, 21: 17.78})  # VCOM label past the I2S_DIN label above it
    for i, net in enumerate(["CODEC_FMT", "CODEC_DEMP", "CODEC_IFMD"]):
        r = R(sh, "10k", (25.4 + i * 10.16, 99.06), fields={"Note": "hardware-mode strap, low; lift to change"})
        sh.connect(r, 1, net)
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    r = R(sh, "5.1R", (40.64, 218.44), rot=90, size="0603", fields={"Note": "isolates the codec VDD from logic noise on +3V3D"})
    sh.connect(r, 1, "+3V3D")
    sh.connect(r, 2, "CODEC_VDD")
    for i, (net, pin, v, sz) in enumerate([("CODEC_VCC", "24", "10u", "0805"), ("CODEC_VCC", "24", "100n", "0402"),
                                           ("CODEC_VDD", "7", "10u", "0805"), ("CODEC_VDD", "7", "100n", "0402")]):
        c = C(sh, v, (60.96 + i * 12.7, 182.88), size=sz, decouples=f"U301 {'VCC' if pin == '24' else 'VDD'} pin {pin}")
        if i in (0, 2):
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            sh.connect(c, 1, net)
        sh.connect(c, 2, "GND", stub=0)
    for i, (v, sz) in enumerate([("10u", "0805"), ("100n", "0402")]):
        c = C(sh, v, (111.76 + i * 12.7, 182.88), size=sz, decouples="U301 VCOM pin 21")
        sh.connect(c, 1, "VCOM")
        sh.connect(c, 2, "GND", stub=0)
    r = R(sh, "1k", (25.4, 180.34), fields={"Note": "RST pull-up (internal 50 kΩ pull-down)"})
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        sh.label(f"AIN{ch}", (jn[0] - 5.08, jn[1]), 180)
        plus = op.p("3") if unit == 1 else op.p("5")
        vc = (plus[0] - 10.16, plus[1])
        cv = C(sh, "100n", (vc[0], vc[1] + 2.54), decouples=f"VCOM at U302 {'pin 3' if unit == 1 else 'pin 5'}")
        sh.wire(plus, vc)
        sh.label("VCOM", vc, 180)
        sh.connect(cv, "2", "GND", stub=0)
        outp = op.p("1") if unit == 1 else op.p("7")
        rout = R(sh, "1k", (ox + 15.24, oy), rot=90)
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    decap(sh, (60.96, 177.8), "10u", "0805", "+5VA", "U401 AVDD bulk")
    decap(sh, (76.2, 177.8), "10u", "0805", "+3V3D", "U401 DVDD pin 34")
    decap(sh, (88.9, 177.8), "100n", "0402", "+3V3D", "U401 DVDD pin 34")
    for i, (v, s, net, note) in enumerate([("1u", "0603", "REFCAP", "U401 REFCAP pin 7, at the pin"),
                                            ("22u", "1206", "REFCAP", "U401 REFCAP pin 7"),
                                            ("10u", "0805", "REFIO", "U401 REFIO pin 5 (internal reference)")]):
        c = C(sh, v, (104.14 + i * 12.7, 180.34), size=s, decouples=note)
        sh.connect(c, 1, net)
        sh.connect(c, 2, "GND", stub=0)
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    minus = op.p("2")
    sh.wire(out, o, (o[0] + 7.62, o[1]))
    sh.wire(o, (o[0], minus[1] + 7.62), (minus[0] - 2.54, minus[1] + 7.62), (minus[0] - 2.54, minus[1]), minus)
    sh.label("OFFSET_REF", (o[0] + 7.62, o[1]), 0)
    sh.label("OFFS_DIV", ((rt.p("2")[0] + rb.p("1")[0]) / 2, plus[1]), 90)
    sh.tie("OFFS_DIV", (rt, "2"), (rb, "1"), (cf, "1"), (op, "3"))
    sh.tie("OFFSET_REF", (op, "1"), (op, "2"))

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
